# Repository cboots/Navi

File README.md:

# Navi
General purpose Nav Computer for drones and robots

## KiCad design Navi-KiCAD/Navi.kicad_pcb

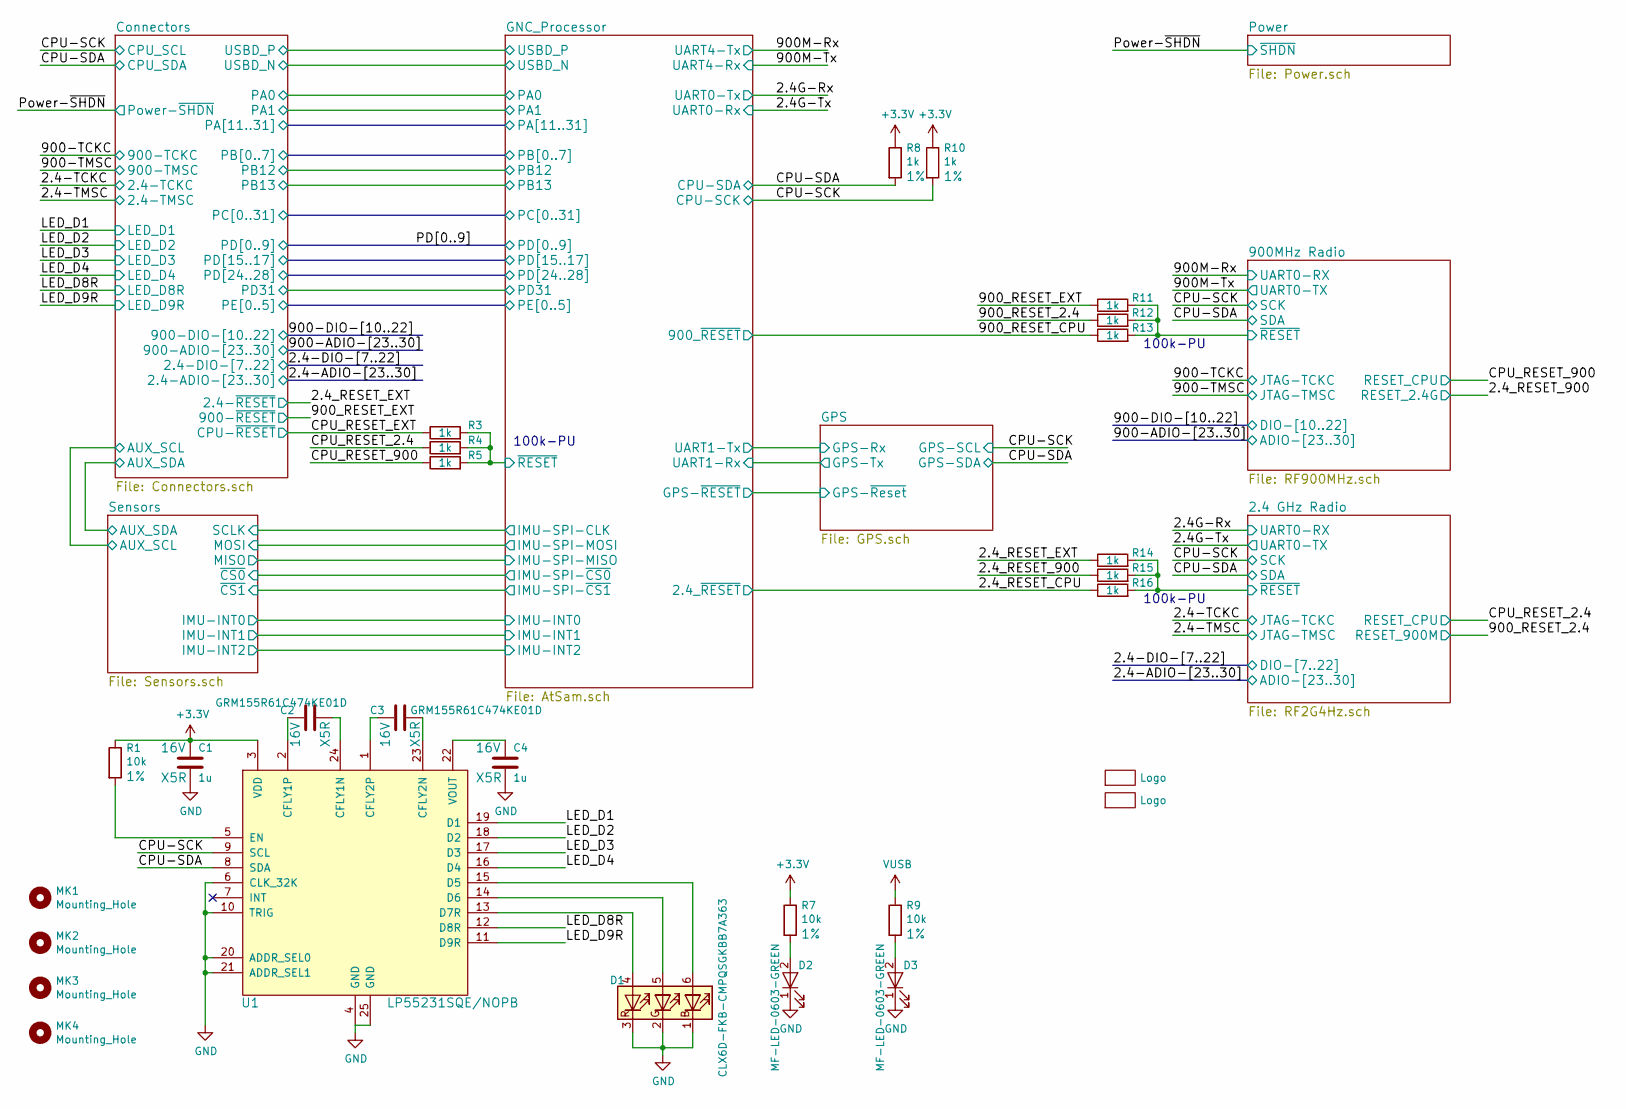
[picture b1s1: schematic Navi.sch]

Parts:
C1, C4: 1u; C_0402; Voltage 16V; Tolerance 20%
C2, C3: GRM155R61C474KE01D; C_0402; Voltage 16V; Tolerance 20%
D1: CLX6D-FKB-CMPQSGKBB7A363; LED_PLCC6_3.4x3.4mm; Manufacturer Part Number CLX6D-FKB-CMPQSGKBB7A363
D2, D3: MF-LED-0603-GREEN; LED_0603
MK1, MK2, MK3, MK4: Mounting_Hole; MountingHole_2.5mm
R1, R7, R9: 10k; R_0402; Tolerance 1%; Voltage 16V
R3, R4, R5, R8, R10, R11, R12, R13, R14, R15, R16: 1k; R_0402; Tolerance 1%; Voltage 16V
U1: LP55231SQE/NOPB; QFN-24-1EP_4x4mm_Pitch0.5mm
U2, U3: Logo; NaviLOGO

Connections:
+3V3: C1.1, R1.1, R7.1, R8.1, R10.1, U1.3 (VDD); also elsewhere on the board
/2.4 GHz Radio/~RESET: R14.2, R15.2, R16.2; also elsewhere on the board
/2.4_RESET_900: R15.1; also elsewhere on the board
/2.4_RESET_CPU: R16.1; also elsewhere on the board
/2.4_RESET_EXT: R14.1; also elsewhere on the board
/900MHz Radio/~RESET: R11.2, R12.2, R13.2; also elsewhere on the board
/900_RESET_2.4: R12.1; also elsewhere on the board
/900_RESET_CPU: R13.1; also elsewhere on the board
/900_RESET_EXT: R11.1; also elsewhere on the board
/CPU-SCK: R10.2, U1.9 (SCL); also elsewhere on the board
/CPU-SDA: R8.2, U1.8 (SDA); also elsewhere on the board
/CPU_RESET_2.4: R4.1; also elsewhere on the board
/CPU_RESET_900: R5.1; also elsewhere on the board
/CPU_RESET_EXT: R3.1; also elsewhere on the board
/GNC_Processor/~RESET: R3.2, R4.2, R5.2; also elsewhere on the board
/LED_D1: U1.19 (D1); also elsewhere on the board
/LED_D2: U1.18 (D2); also elsewhere on the board
/LED_D3: U1.17 (D3); also elsewhere on the board
/LED_D4: U1.16 (D4); also elsewhere on the board
/LED_D8R: U1.12 (D8R); also elsewhere on the board
/LED_D9R: U1.11 (D9R); also elsewhere on the board
GND: C1.2, C4.2, D1.1 (RK), D1.2 (GK), D1.3 (BK), D2.1 (K), D3.1 (K), U1.4 (GND), U1.6 (CLK_32K), U1.10 (TRIG), U1.20 (ADDR_SEL0), U1.21 (ADDR_SEL1), U1.25 (GND); also elsewhere on the board
unnamed: C2.1, U1.2 (CFLY1P)
unnamed: C2.2, U1.24 (CFLY1N)
unnamed: C3.1, U1.1 (CFLY2P)
unnamed: C3.2, U1.23 (CFLY2N)
unnamed: C4.1, U1.22 (VOUT)
unnamed: D1.4 (BA), U1.13 (D7R)
unnamed: D1.5 (GA), U1.14 (D6)
unnamed: D1.6 (RA), U1.15 (D5)
unnamed: D2.2 (A), R7.2
unnamed: D3.2 (A), R9.2
unnamed: R1.2, U1.5 (EN)
VUSB: R9.1; also elsewhere on the board

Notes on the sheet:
100k-PU

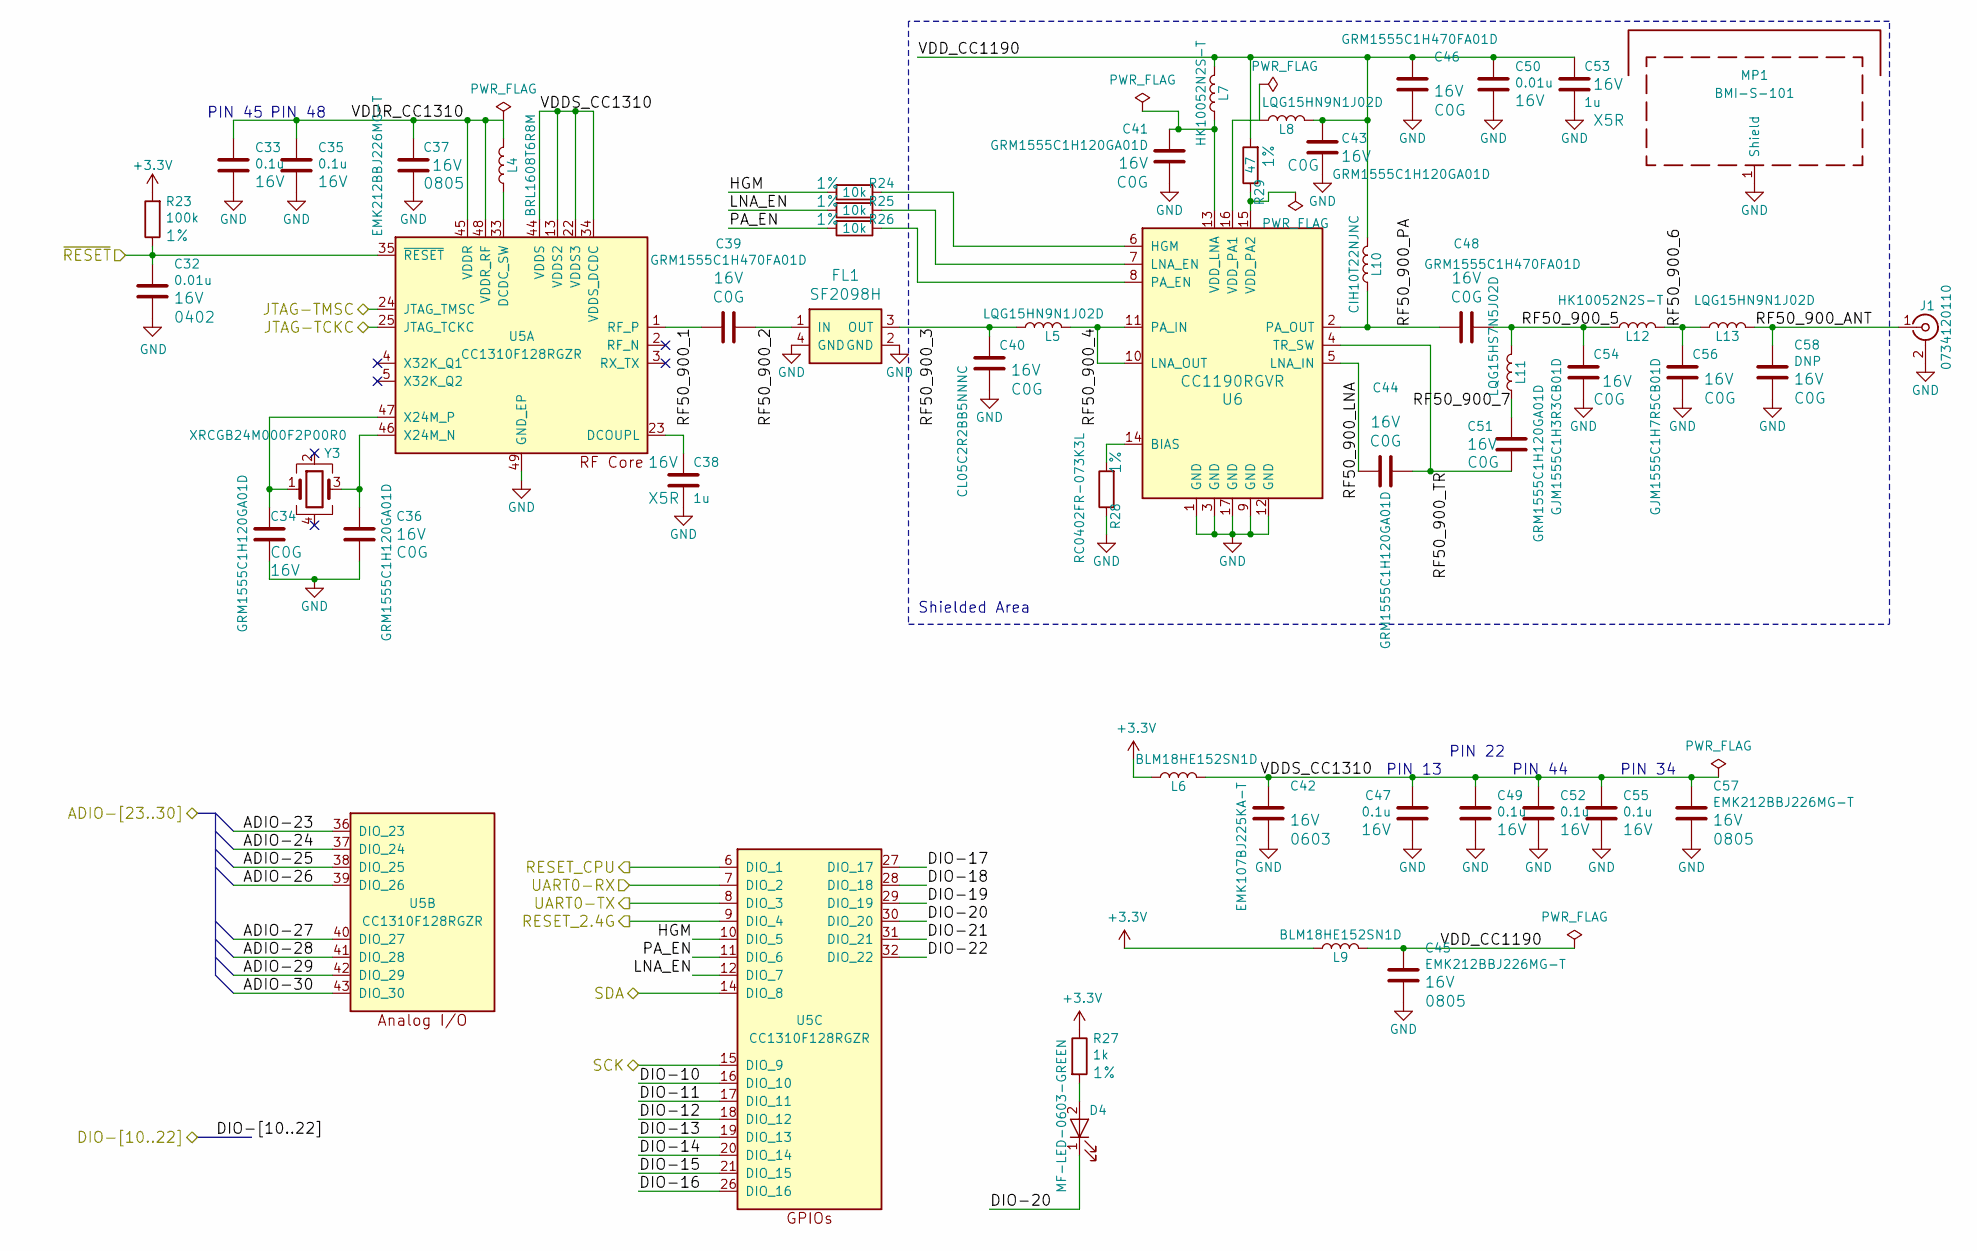
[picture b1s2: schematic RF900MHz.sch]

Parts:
C32, C50: 0.01u; C_0402; Voltage 16V; Tolerance 20%
C33, C35, C47, C49, C52, C55: 0.1u; C_0402; Voltage 16V; Tolerance 20%
C34, C36, C41, C43, C44, C51: GRM1555C1H120GA01D; C_0402; Voltage 16V; Tolerance 20%
C37, C45, C57: EMK212BBJ226MG-T; C_0805; Voltage 16V; Tolerance 20%
C38, C53: 1u; C_0402; Voltage 16V; Tolerance 20%
C39, C46, C48: GRM1555C1H470FA01D; C_0402; Voltage 16V; Tolerance 20%
C40: CL05C2R2BB5NNNC; C_0402; Voltage 16V; Tolerance 20%
C42: EMK107BJ225KA-T; C_0603; Voltage 16V; Tolerance 20%
C54: GJM1555C1H3R3CB01D; C_0402; Voltage 16V; Tolerance 20%
C56: GJM1555C1H7R5CB01D; C_0402; Voltage 16V; Tolerance 20%
C58: DNP; C_0402; Voltage 16V; Tolerance 20%
D4: MF-LED-0603-GREEN; LED_0603
FL1: SF2098H; SM2016-4
J1: 0734120110; Molex_Microcoaxial_RF
L4: BRL1608T6R8M; L_0603
L5, L8, L13: LQG15HN9N1J02D; L_0402
L6, L9: BLM18HE152SN1D; L_0603
L7, L12: HK10052N2S-T; L_0402
L10: CIH10T22NJNC; L_0603
L11: LQG15HS7N5J02D; L_0402
MP1: BMI-S-101; Laird_Technologies_BMI-S-101_13.66x12.70mm
R23: 100k; R_0402; Tolerance 1%; Voltage 16V
R24, R25, R26: 10k; R_0402; Tolerance 1%; Voltage 16V
R27: 1k; R_0402; Tolerance 1%; Voltage 16V
R28: RC0402FR-073K3L; R_0402; Tolerance 1%; Voltage 16V
R29: 47; R_0402; Tolerance 1%; Voltage 16V
U5: CC1310F128RGZR; QFN-48-1EP_7x7mm_Pitch0.5mm
U6: CC1190RGVR; QFN-16-1EP_4x4mm_Pitch0.65mm
Y3: XRCGB24M000F2P00R0; Crystal_SMD_2016-4pin_2.0x1.6mm

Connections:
+3V3: L6.1, L9.1, R23.2, R27.1; also elsewhere on the board
/2.4_RESET_900: U5.9 (DIO_4); also elsewhere on the board
/900-TCKC: U5.25 (JTAG_TCKC); also elsewhere on the board
/900-TMSC: U5.24 (JTAG_TMSC); also elsewhere on the board
/900M-Rx: U5.7 (DIO_2); also elsewhere on the board
/900M-Tx: U5.8 (DIO_3); also elsewhere on the board
/900MHz Radio/HGM: R24.2, U5.10 (DIO_5)
/900MHz Radio/LNA_EN: R25.2, U5.12 (DIO_7)
/900MHz Radio/PA_EN: R26.2, U5.11 (DIO_6)
/900MHz Radio/RF50_900_1: C39.1, U5.1 (RF_P)
/900MHz Radio/RF50_900_2: C39.2, FL1.1 (IN)
/900MHz Radio/RF50_900_3: C40.2, FL1.3 (OUT), L5.1
/900MHz Radio/RF50_900_4: L5.2, U6.10 (LNA_OUT), U6.11 (PA_IN)
/900MHz Radio/RF50_900_5: C48.2, C54.1, L11.2, L12.1
/900MHz Radio/RF50_900_6: C56.1, L12.2, L13.1
/900MHz Radio/RF50_900_7: C51.2, L11.1
/900MHz Radio/RF50_900_ANT: C58.1, J1.1 (In), L13.2
/900MHz Radio/RF50_900_LNA: C44.2, U6.5 (LNA_IN)
/900MHz Radio/RF50_900_PA: C48.1, L10.1, U6.2 (PA_OUT)
/900MHz Radio/RF50_900_TR: C44.1, C51.1, U6.4 (TR_SW)
/900MHz Radio/VDDR_CC1310: C33.1, C35.1, C37.1, L4.2, U5.45 (VDDR), U5.48 (VDDR_RF)
/900MHz Radio/VDDS_CC1310: C42.1, C47.1, C49.1, C52.1, C55.1, C57.1, L6.2, U5.13 (VDDS2), U5.22 (VDDS3), U5.34 (VDDS_DCDC), U5.44 (VDDS)
/900MHz Radio/VDD_CC1190: C43.2, C45.1, C46.1, C50.1, C53.1, L7.2, L8.2, L9.2, L10.2, R29.2
/900MHz Radio/~RESET: C32.1, R23.1, U5.35 (~RESET); also elsewhere on the board
/CPU-SCK: U5.15 (DIO_9); also elsewhere on the board
/CPU-SDA: U5.14 (DIO_8); also elsewhere on the board
/CPU_RESET_900: U5.6 (DIO_1); also elsewhere on the board
/Connectors/900-ADIO-23: U5.36 (DIO_23); also elsewhere on the board
/Connectors/900-ADIO-24: U5.37 (DIO_24); also elsewhere on the board
/Connectors/900-ADIO-25: U5.38 (DIO_25); also elsewhere on the board
/Connectors/900-ADIO-26: U5.39 (DIO_26); also elsewhere on the board
/Connectors/900-ADIO-27: U5.40 (DIO_27); also elsewhere on the board
/Connectors/900-ADIO-28: U5.41 (DIO_28); also elsewhere on the board
/Connectors/900-ADIO-29: U5.42 (DIO_29); also elsewhere on the board
/Connectors/900-ADIO-30: U5.43 (DIO_30); also elsewhere on the board
/Connectors/900-DIO-10: U5.16 (DIO_10); also elsewhere on the board
/Connectors/900-DIO-11: U5.17 (DIO_11); also elsewhere on the board
/Connectors/900-DIO-12: U5.18 (DIO_12); also elsewhere on the board
/Connectors/900-DIO-13: U5.19 (DIO_13); also elsewhere on the board
/Connectors/900-DIO-14: U5.20 (DIO_14); also elsewhere on the board
/Connectors/900-DIO-15: U5.21 (DIO_15); also elsewhere on the board
/Connectors/900-DIO-16: U5.26 (DIO_16); also elsewhere on the board
/Connectors/900-DIO-17: U5.27 (DIO_17); also elsewhere on the board
/Connectors/900-DIO-18: U5.28 (DIO_18); also elsewhere on the board
/Connectors/900-DIO-19: U5.29 (DIO_19); also elsewhere on the board
/Connectors/900-DIO-20: D4.1 (K), U5.30 (DIO_20); also elsewhere on the board
/Connectors/900-DIO-21: U5.31 (DIO_21); also elsewhere on the board
/Connectors/900-DIO-22: U5.32 (DIO_22); also elsewhere on the board
GND: C32.2, C33.2, C34.1, C35.2, C36.1, C37.2, C38.2, C40.1, C41.1, C42.2, C43.1, C45.2, C46.2, C47.2, C49.2, C50.2, C52.2, C53.2, C54.2, C55.2, C56.2, C57.2, C58.2, FL1.2 (GND), FL1.4 (GND), J1.2 (Ext), MP1.1, R28.1, U5.49 (GND_EP), U6.1 (GND), U6.3 (GND), U6.9 (GND), U6.12 (GND), U6.17 (GND); also elsewhere on the board
unnamed: C34.2, U5.47 (X24M_P), Y3.1
unnamed: C36.2, U5.46 (X24M_N), Y3.3
unnamed: C38.1, U5.23 (DCOUPL)
unnamed: C41.2, L7.1, U6.13 (VDD_LNA)
unnamed: D4.2 (A), R27.2
unnamed: L4.1, U5.33 (DCDC_SW)
unnamed: L8.1, U6.16 (VDD_PA1)
unnamed: R24.1, U6.6 (HGM)
unnamed: R25.1, U6.7 (LNA_EN)
unnamed: R26.1, U6.8 (PA_EN)
unnamed: R28.2, U6.14 (BIAS)
unnamed: R29.1, U6.15 (VDD_PA2)

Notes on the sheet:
Shielded Area
PIN 13
PIN 22
PIN 44
PIN 34
PIN 45
PIN 48

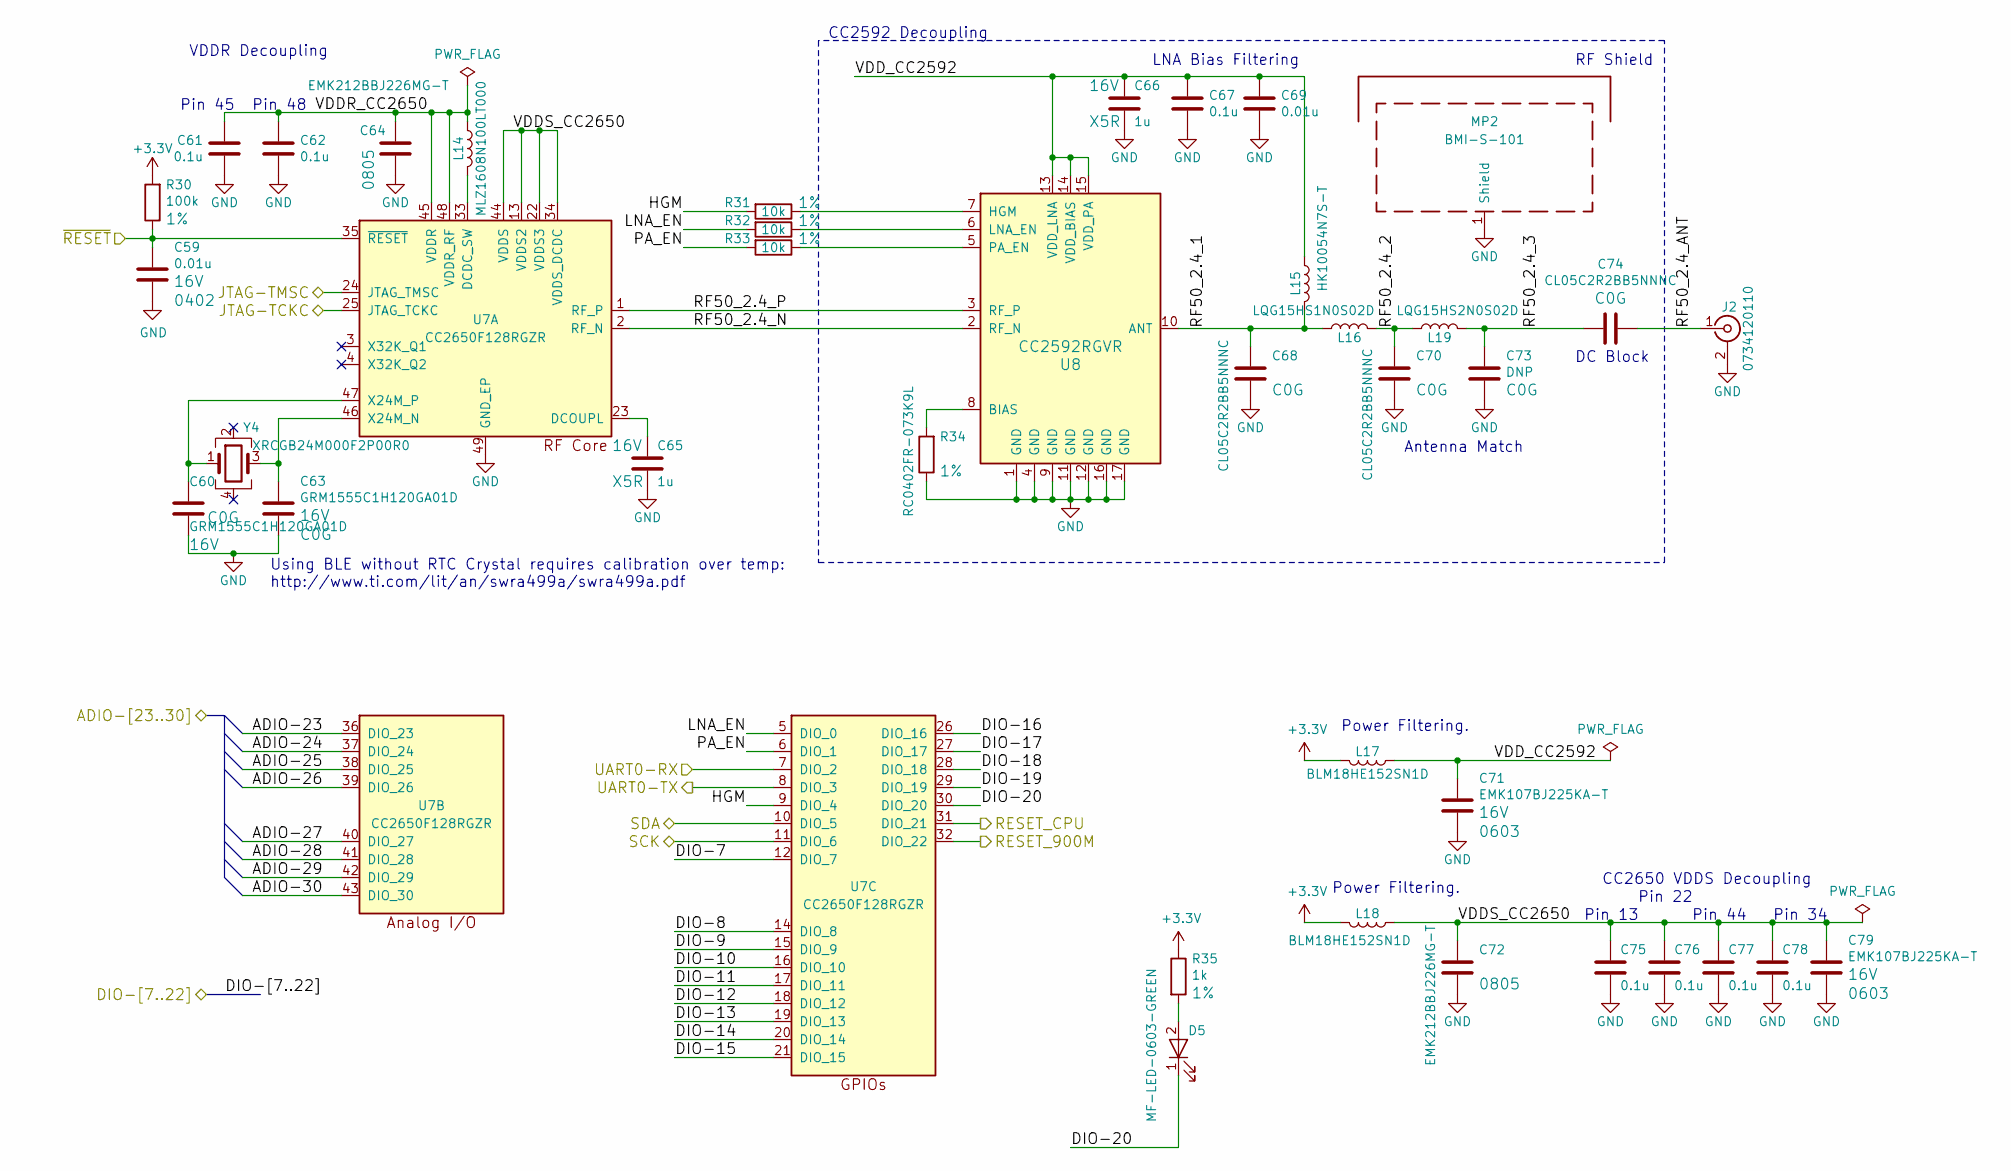
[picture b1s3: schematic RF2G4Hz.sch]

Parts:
C59, C69: 0.01u; C_0402; Voltage 16V; Tolerance 20%
C60, C63: GRM1555C1H120GA01D; C_0402; Voltage 16V; Tolerance 20%
C61, C62, C67, C75, C76, C77, C78: 0.1u; C_0402; Voltage 16V; Tolerance 20%
C64, C72: EMK212BBJ226MG-T; C_0805; Voltage 16V; Tolerance 20%
C65, C66: 1u; C_0402; Voltage 16V; Tolerance 20%
C68, C70, C74: CL05C2R2BB5NNNC; C_0402; Voltage 16V; Tolerance 20%
C71, C79: EMK107BJ225KA-T; C_0603; Voltage 16V; Tolerance 20%
C73: DNP; C_0402; Voltage 16V; Tolerance 20%
D5: MF-LED-0603-GREEN; LED_0603
J2: 0734120110; Molex_Microcoaxial_RF
L14: MLZ1608N100LT000; L_0603
L15: HK10054N7S-T; L_0402
L16: LQG15HS1N0S02D; L_0402
L17, L18: BLM18HE152SN1D; L_0603
L19: LQG15HS2N0S02D; L_0402
MP2: BMI-S-101; Laird_Technologies_BMI-S-101_13.66x12.70mm
R30: 100k; R_0402; Tolerance 1%; Voltage 16V
R31, R32, R33: 10k; R_0402; Tolerance 1%; Voltage 16V
R34: RC0402FR-073K9L; R_0402; Tolerance 1%; Voltage 16V
R35: 1k; R_0402; Tolerance 1%; Voltage 16V
U7: CC2650F128RGZR; QFN-48-1EP_7x7mm_Pitch0.5mm
U8: CC2592RGVR; QFN-16-1EP_4x4mm_Pitch0.65mm
Y4: XRCGB24M000F2P00R0; Crystal_SMD_2016-4pin_2.0x1.6mm

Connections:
+3V3: L17.2, L18.2, R30.2, R35.1; also elsewhere on the board
/2.4 GHz Radio/HGM: R31.2, U7.9 (DIO_4)
/2.4 GHz Radio/LNA_EN: R32.2, U7.5 (DIO_0)
/2.4 GHz Radio/PA_EN: R33.2, U7.6 (DIO_1)
/2.4 GHz Radio/RF50_2.4_1: C68.1, L15.2, L16.1, U8.10 (ANT)
/2.4 GHz Radio/RF50_2.4_2: C70.1, L16.2, L19.1
/2.4 GHz Radio/RF50_2.4_3: C73.1, C74.2, L19.2
/2.4 GHz Radio/RF50_2.4_ANT: C74.1, J2.1 (In)
/2.4 GHz Radio/RF50_2.4_N: U7.2 (RF_N), U8.2 (RF_N)
/2.4 GHz Radio/RF50_2.4_P: U7.1 (RF_P), U8.3 (RF_P)
/2.4 GHz Radio/VDDR_CC2650: C61.1, C62.1, C64.1, L14.1, U7.45 (VDDR), U7.48 (VDDR_RF)
/2.4 GHz Radio/VDDS_CC2650: C72.1, C75.1, C76.1, C77.1, C78.1, C79.1, L18.1, U7.13 (VDDS2), U7.22 (VDDS3), U7.34 (VDDS_DCDC), U7.44 (VDDS)
/2.4 GHz Radio/VDD_CC2592: C66.1, C67.1, C69.1, C71.1, L15.1, L17.1, U8.13 (VDD_LNA), U8.14 (VDD_BIAS), U8.15 (VDD_PA)
/2.4 GHz Radio/~RESET: C59.1, R30.1, U7.35 (~RESET); also elsewhere on the board
/2.4-TCKC: U7.25 (JTAG_TCKC); also elsewhere on the board
/2.4-TMSC: U7.24 (JTAG_TMSC); also elsewhere on the board
/2.4G-Rx: U7.7 (DIO_2); also elsewhere on the board
/2.4G-Tx: U7.8 (DIO_3); also elsewhere on the board
/900_RESET_2.4: U7.32 (DIO_22); also elsewhere on the board
/CPU-SCK: U7.11 (DIO_6); also elsewhere on the board
/CPU-SDA: U7.10 (DIO_5); also elsewhere on the board
/CPU_RESET_2.4: U7.31 (DIO_21); also elsewhere on the board
/Connectors/2.4-ADIO-23: U7.36 (DIO_23); also elsewhere on the board
/Connectors/2.4-ADIO-24: U7.37 (DIO_24); also elsewhere on the board
/Connectors/2.4-ADIO-25: U7.38 (DIO_25); also elsewhere on the board
/Connectors/2.4-ADIO-26: U7.39 (DIO_26); also elsewhere on the board
/Connectors/2.4-ADIO-27: U7.40 (DIO_27); also elsewhere on the board
/Connectors/2.4-ADIO-28: U7.41 (DIO_28); also elsewhere on the board
/Connectors/2.4-ADIO-29: U7.42 (DIO_29); also elsewhere on the board
/Connectors/2.4-ADIO-30: U7.43 (DIO_30); also elsewhere on the board
/Connectors/2.4-DIO-7: U7.12 (DIO_7); also elsewhere on the board
/Connectors/2.4-DIO-8: U7.14 (DIO_8); also elsewhere on the board
/Connectors/2.4-DIO-9: U7.15 (DIO_9); also elsewhere on the board
/Connectors/2.4-DIO-10: U7.16 (DIO_10); also elsewhere on the board
/Connectors/2.4-DIO-11: U7.17 (DIO_11); also elsewhere on the board
/Connectors/2.4-DIO-12: U7.18 (DIO_12); also elsewhere on the board
/Connectors/2.4-DIO-13: U7.19 (DIO_13); also elsewhere on the board
/Connectors/2.4-DIO-14: U7.20 (DIO_14); also elsewhere on the board
/Connectors/2.4-DIO-15: U7.21 (DIO_15); also elsewhere on the board
/Connectors/2.4-DIO-16: U7.26 (DIO_16); also elsewhere on the board
/Connectors/2.4-DIO-17: U7.27 (DIO_17); also elsewhere on the board
/Connectors/2.4-DIO-18: U7.28 (DIO_18); also elsewhere on the board
/Connectors/2.4-DIO-19: U7.29 (DIO_19); also elsewhere on the board
/Connectors/2.4-DIO-20: D5.1 (K), U7.30 (DIO_20); also elsewhere on the board
GND: C59.2, C60.1, C61.2, C62.2, C63.1, C64.2, C65.2, C66.2, C67.2, C68.2, C69.2, C70.2, C71.2, C72.2, C73.2, C75.2, C76.2, C77.2, C78.2, C79.2, J2.2 (Ext), MP2.1, R34.1, U7.49 (GND_EP), U8.1 (GND), U8.4 (GND), U8.9 (GND), U8.11 (GND), U8.12 (GND), U8.16 (GND), U8.17 (GND); also elsewhere on the board
unnamed: C60.2, U7.47 (X24M_P), Y4.1
unnamed: C63.2, U7.46 (X24M_N), Y4.3
unnamed: C65.1, U7.23 (DCOUPL)
unnamed: D5.2 (A), R35.2
unnamed: L14.2, U7.33 (DCDC_SW)
unnamed: R31.1, U8.7 (HGM)
unnamed: R32.1, U8.6 (LNA_EN)
unnamed: R33.1, U8.5 (PA_EN)
unnamed: R34.2, U8.8 (BIAS)

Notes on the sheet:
RF Shield
CC2592 Decoupling
LNA Bias Filtering
Antenna Match
DC Block
Power Filtering.
CC2650 VDDS Decoupling
Pin 13
Pin 22
Pin 44
Pin 34
Pin 45
Pin 48
VDDR Decoupling
Using BLE without RTC Crystal requires calibration over temp: http://www.ti.com/lit/an/swra499a/swra499a.pdf

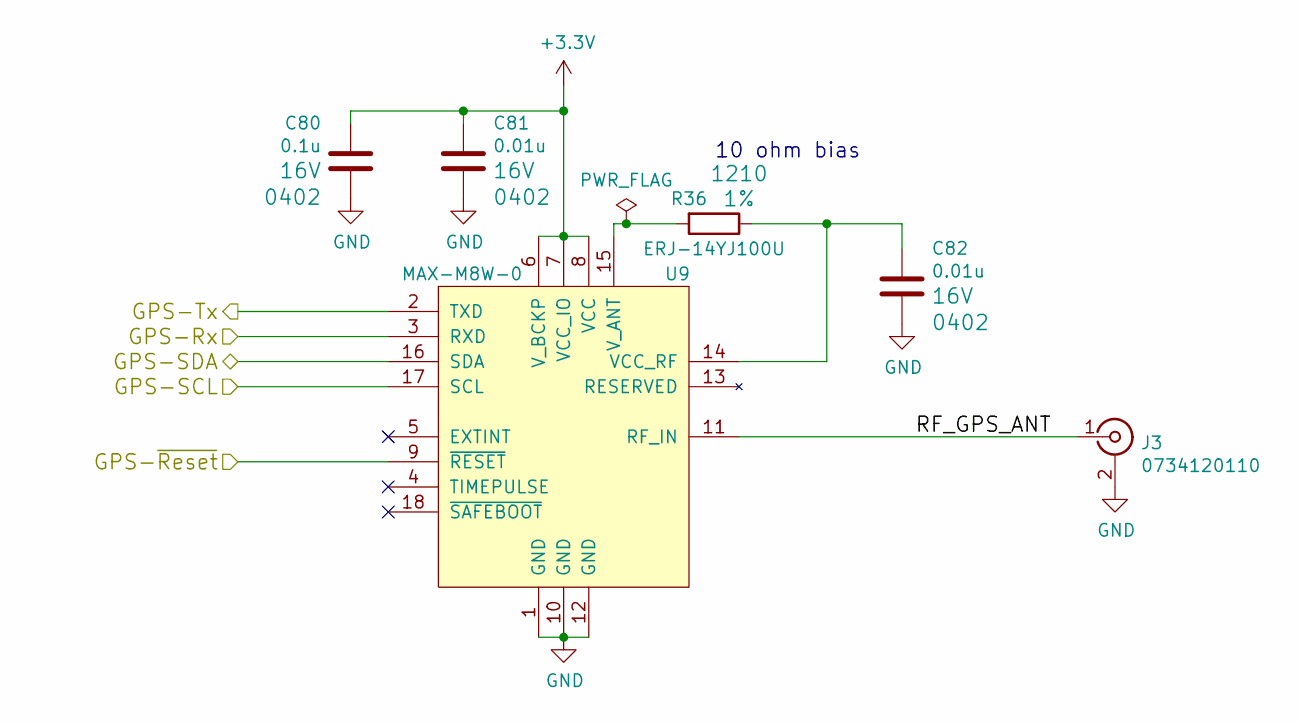
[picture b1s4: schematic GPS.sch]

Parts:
C80: 0.1u; C_0402; Voltage 16V; Tolerance 20%
C81, C82: 0.01u; C_0402; Voltage 16V; Tolerance 20%
J3: 0734120110; Molex_Microcoaxial_RF
R36: ERJ-14YJ100U; R_1210; Tolerance 1%; Voltage 16V
U9: MAX-M8W-0; U-BLOX-MAX

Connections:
+3V3: C80.1, C81.1, U9.6 (V_BCKP), U9.7 (VCC_IO), U9.8 (VCC); also elsewhere on the board
/CPU-SCK: U9.17 (SCL); also elsewhere on the board
/CPU-SDA: U9.16 (SDA); also elsewhere on the board
/GNC_Processor/GPS-~RESET: U9.9 (~RESET); also elsewhere on the board
/GPS/GPS-Rx: U9.3 (RXD); also elsewhere on the board
/GPS/GPS-Tx: U9.2 (TXD); also elsewhere on the board
/GPS/RF_GPS_ANT: J3.1 (In), U9.11 (RF_IN)
GND: C80.2, C81.2, C82.2, J3.2 (Ext), U9.1 (GND), U9.10 (GND), U9.12 (GND); also elsewhere on the board
unnamed: C82.1, R36.1, U9.14 (VCC_RF)
unnamed: R36.2, U9.15 (V_ANT)

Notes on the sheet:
10 ohm bias

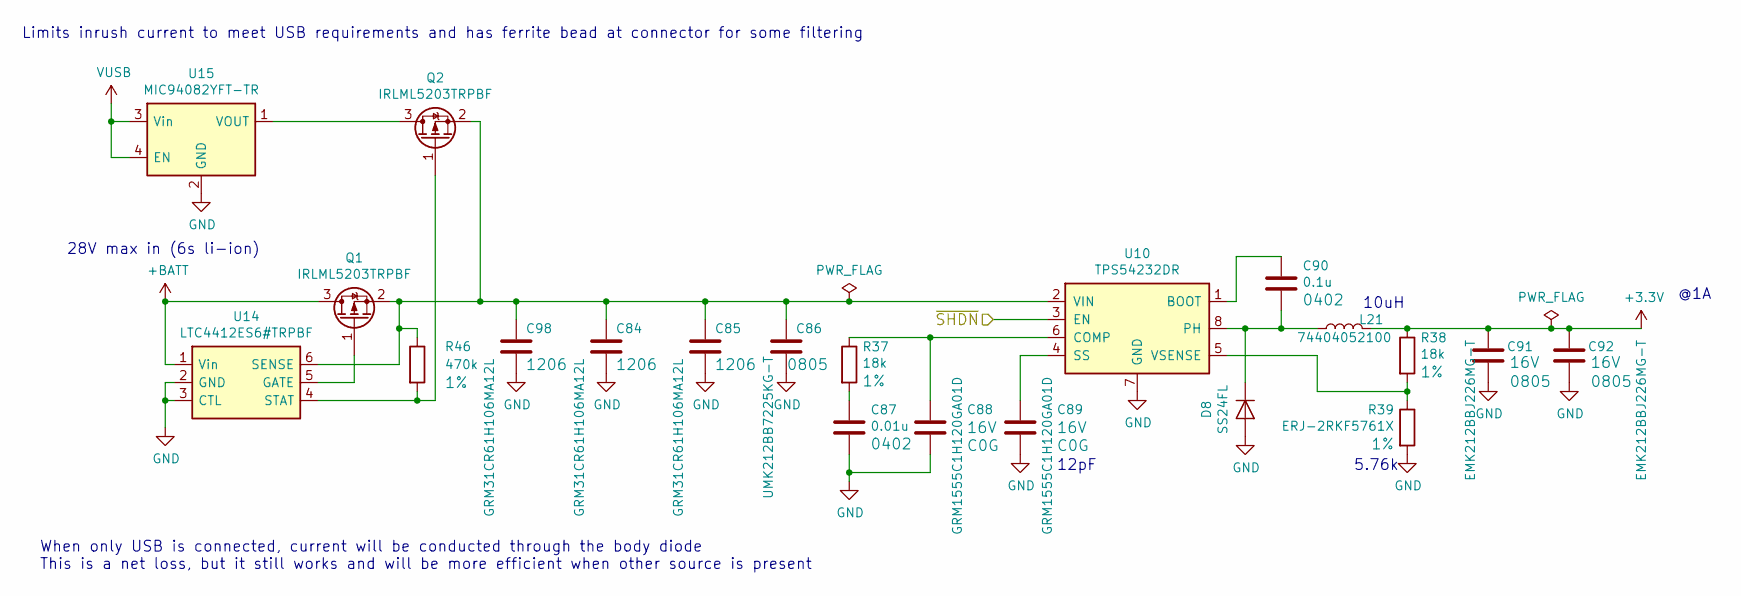
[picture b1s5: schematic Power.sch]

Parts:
C84, C85, C98: GRM31CR61H106MA12L; C_1206; Voltage 50V; Tolerance 20%
C86: UMK212BB7225KG-T; C_0805; Voltage 50V; Tolerance 20%
C87: 0.01u; C_0402; Voltage 16V; Tolerance 20%
C88, C89: GRM1555C1H120GA01D; C_0402; Voltage 16V; Tolerance 20%
C90: 0.1u; C_0402; Voltage 16V; Tolerance 20%
C91, C92: EMK212BBJ226MG-T; C_0805; Voltage 16V; Tolerance 20%
D8: SS24FL; D_SOD-123F
L21: 74404052100; Inductor_Wurth_LQS-5020
Q1, Q2: IRLML5203TRPBF; SOT-23
R37, R38: 18k; R_0402; Tolerance 1%; Voltage 16V
R39: ERJ-2RKF5761X; R_0402; Tolerance 1%; Voltage 16V
R46: 470k; R_0402; Tolerance 1%; Voltage 16V
U10: TPS54232DR; SOIC-8_3.9x4.9mm_Pitch1.27mm
U14: LTC4412ES6#TRPBF; TSOT-23-6_MK06A
U15: MIC94082YFT-TR; TMLF085085D-4LD-9

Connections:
+3V3: C91.1, C92.1, L21.2, R38.1; also elsewhere on the board
+BATT: Q1.3 (D), U14.1 (Vin); also elsewhere on the board
/Power-~SHDN~: U10.3 (EN); also elsewhere on the board
GND: C84.2, C85.2, C86.2, C87.2, C88.1, C89.1, C91.2, C92.2, C98.2, D8.2 (A), R39.2, U10.7 (GND), U14.2 (GND), U14.3 (CTL), U15.2 (GND); also elsewhere on the board
unnamed: C84.1, C85.1, C86.1, C98.1, Q1.2 (S), Q2.2 (S), R46.1, U10.2 (VIN), U14.6 (SENSE)
unnamed: C87.1, R37.2
unnamed: C88.2, R37.1, U10.6 (COMP)
unnamed: C89.2, U10.4 (SS)
unnamed: C90.1, D8.1 (K), L21.1, U10.8 (PH)
unnamed: C90.2, U10.1 (BOOT)
unnamed: Q1.1 (G), U14.5 (GATE)
unnamed: Q2.1 (G), R46.2, U14.4 (STAT)
unnamed: Q2.3 (D), U15.1 (VOUT)
unnamed: R38.2, R39.1, U10.5 (VSENSE)
VUSB: U15.3 (Vin), U15.4 (EN); also elsewhere on the board

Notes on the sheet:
@1A
12pF
5.76k
10uH
Limits inrush current to meet USB requirements and has ferrite bead at connector for some filtering
28V max in (6s li-ion)
When only USB is connected, current will be conducted through the body diode This is a net loss, but it still works and will be more efficient when other source is present

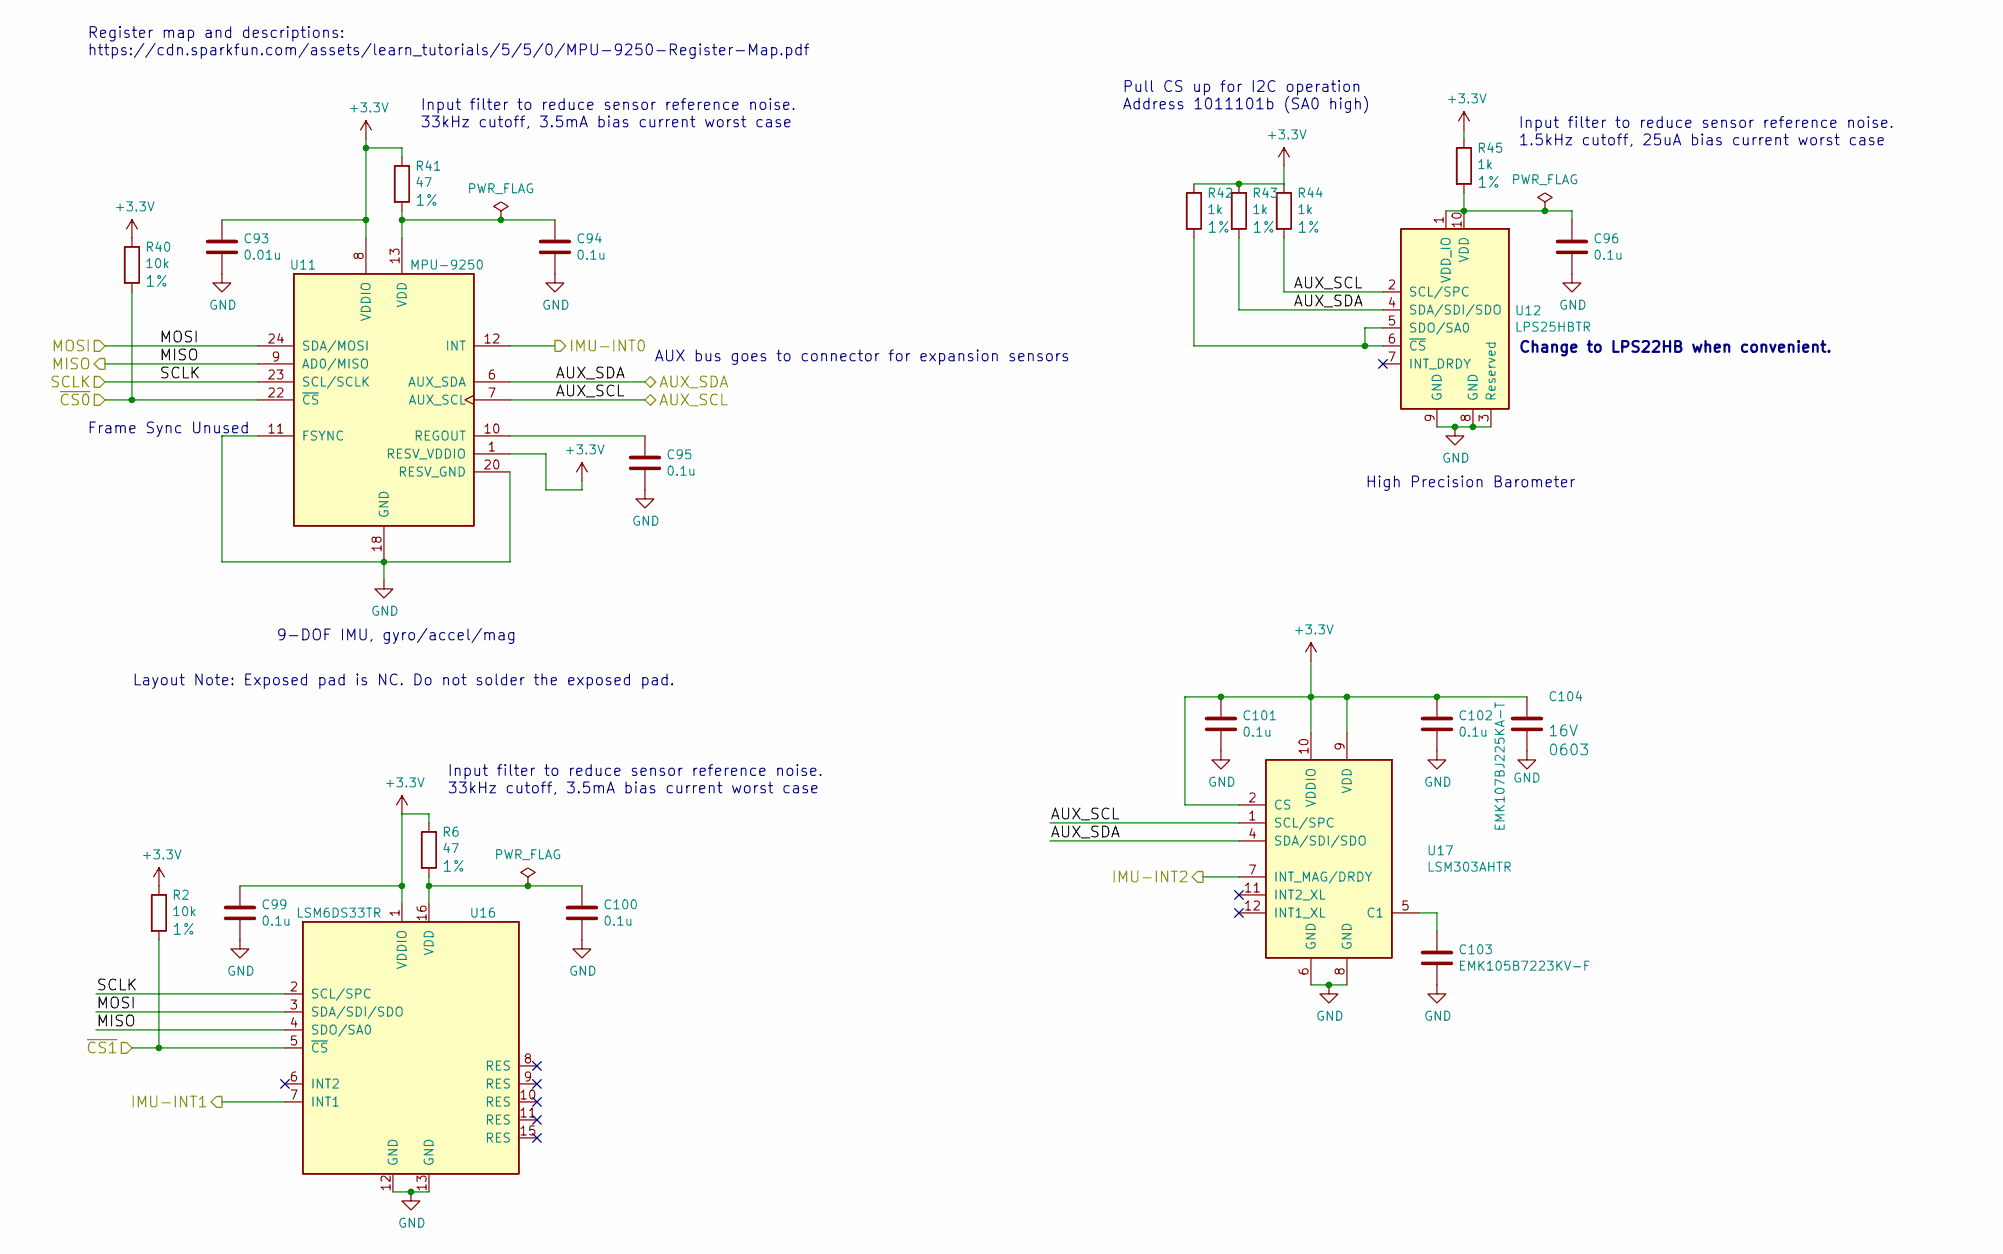
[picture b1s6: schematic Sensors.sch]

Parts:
C93: 0.01u; C_0402; Voltage 16V; Tolerance 20%
C94, C95, C96, C99, C100, C101, C102: 0.1u; C_0402; Voltage 16V; Tolerance 20%
C103: EMK105B7223KV-F; C_0402; Voltage 16V; Tolerance 20%
C104: EMK107BJ225KA-T; C_0603; Voltage 16V; Tolerance 20%
R2, R40: 10k; R_0402; Tolerance 1%; Voltage 16V
R6, R41: 47; R_0402; Tolerance 1%; Voltage 16V
R42, R43, R44, R45: 1k; R_0402; Tolerance 1%; Voltage 16V
U11: MPU-9250; QFN-24-1EP_3x3mm_Pitch0.4mm_MPU-9250
U12: LPS25HBTR; HLGA-10L_2.5x2.5mm_Pitch0.6mm
U16: LSM6DS33TR; LGA-16L_3x3mm_Pitch0.5mm
U17: LSM303AHTR; LGA-12_2x2mm_Pitch0.5mm

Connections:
+3V3: C93.1, C99.1, C101.1, C102.1, C104.1, R2.1, R6.1, R40.1, R41.1, R42.1, R43.1, R44.1, R45.1, U11.1 (RESV_VDDIO), U11.8 (VDDIO), U16.1 (VDDIO), U17.2 (CS), U17.9 (VDD), U17.10 (VDDIO); also elsewhere on the board
/Connectors/AUX_SCL: R44.2, U11.7 (AUX_SCL), U12.2 (SCL/SPC), U17.1 (SCL/SPC); also elsewhere on the board
/Connectors/AUX_SDA: R43.2, U11.6 (AUX_SDA), U12.4 (SDA/SDI/SDO), U17.4 (SDA/SDI/SDO); also elsewhere on the board
/GNC_Processor/IMU-INT0: U11.12 (INT); also elsewhere on the board
/GNC_Processor/IMU-INT1: U16.7 (INT1); also elsewhere on the board
/GNC_Processor/IMU-INT2: U17.7 (INT_MAG/DRDY); also elsewhere on the board
/GNC_Processor/IMU-SPI-CLK: U11.23 (SCL/SCLK), U16.2 (SCL/SPC); also elsewhere on the board
/GNC_Processor/IMU-SPI-MISO: U11.9 (AD0/MISO), U16.4 (SDO/SA0); also elsewhere on the board
/GNC_Processor/IMU-SPI-MOSI: U11.24 (SDA/MOSI), U16.3 (SDA/SDI/SDO); also elsewhere on the board
/GNC_Processor/IMU-SPI-~CS0: R40.2, U11.22 (~CS); also elsewhere on the board
/GNC_Processor/IMU-SPI-~CS1: R2.2, U16.5 (~CS); also elsewhere on the board
GND: C93.2, C94.2, C95.2, C96.2, C99.2, C100.2, C101.2, C102.2, C103.2, C104.2, U11.11 (FSYNC), U11.18 (GND), U11.20 (RESV_GND), U12.3 (Reserved), U12.8 (GND), U12.9 (GND), U16.12 (GND), U16.13 (GND), U17.6 (GND), U17.8 (GND); also elsewhere on the board
unnamed: C94.1, R41.2, U11.13 (VDD)
unnamed: C95.1, U11.10 (REGOUT)
unnamed: C96.1, R45.2, U12.1 (VDD_IO), U12.10 (VDD)
unnamed: C100.1, R6.2, U16.16 (VDD)
unnamed: C103.1, U17.5 (C1)
unnamed: R42.2, U12.5 (SDO/SA0), U12.6 (~CS)

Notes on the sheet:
Input filter to reduce sensor reference noise. 1.5kHz cutoff, 25uA bias current worst case
Pull CS up for I2C operation Address 1011101b (SA0 high)
High Precision Barometer
9-DOF IMU, gyro/accel/mag
Input filter to reduce sensor reference noise. 33kHz cutoff, 3.5mA bias current worst case
Frame Sync Unused
Register map and descriptions: https://cdn.sparkfun.com/assets/learn_tutorials/5/5/0/MPU-9250-Register-Map.pdf
AUX bus goes to connector for expansion sensors
Layout Note: Exposed pad is NC. Do not solder the exposed pad.
Change to LPS22HB when convenient.
